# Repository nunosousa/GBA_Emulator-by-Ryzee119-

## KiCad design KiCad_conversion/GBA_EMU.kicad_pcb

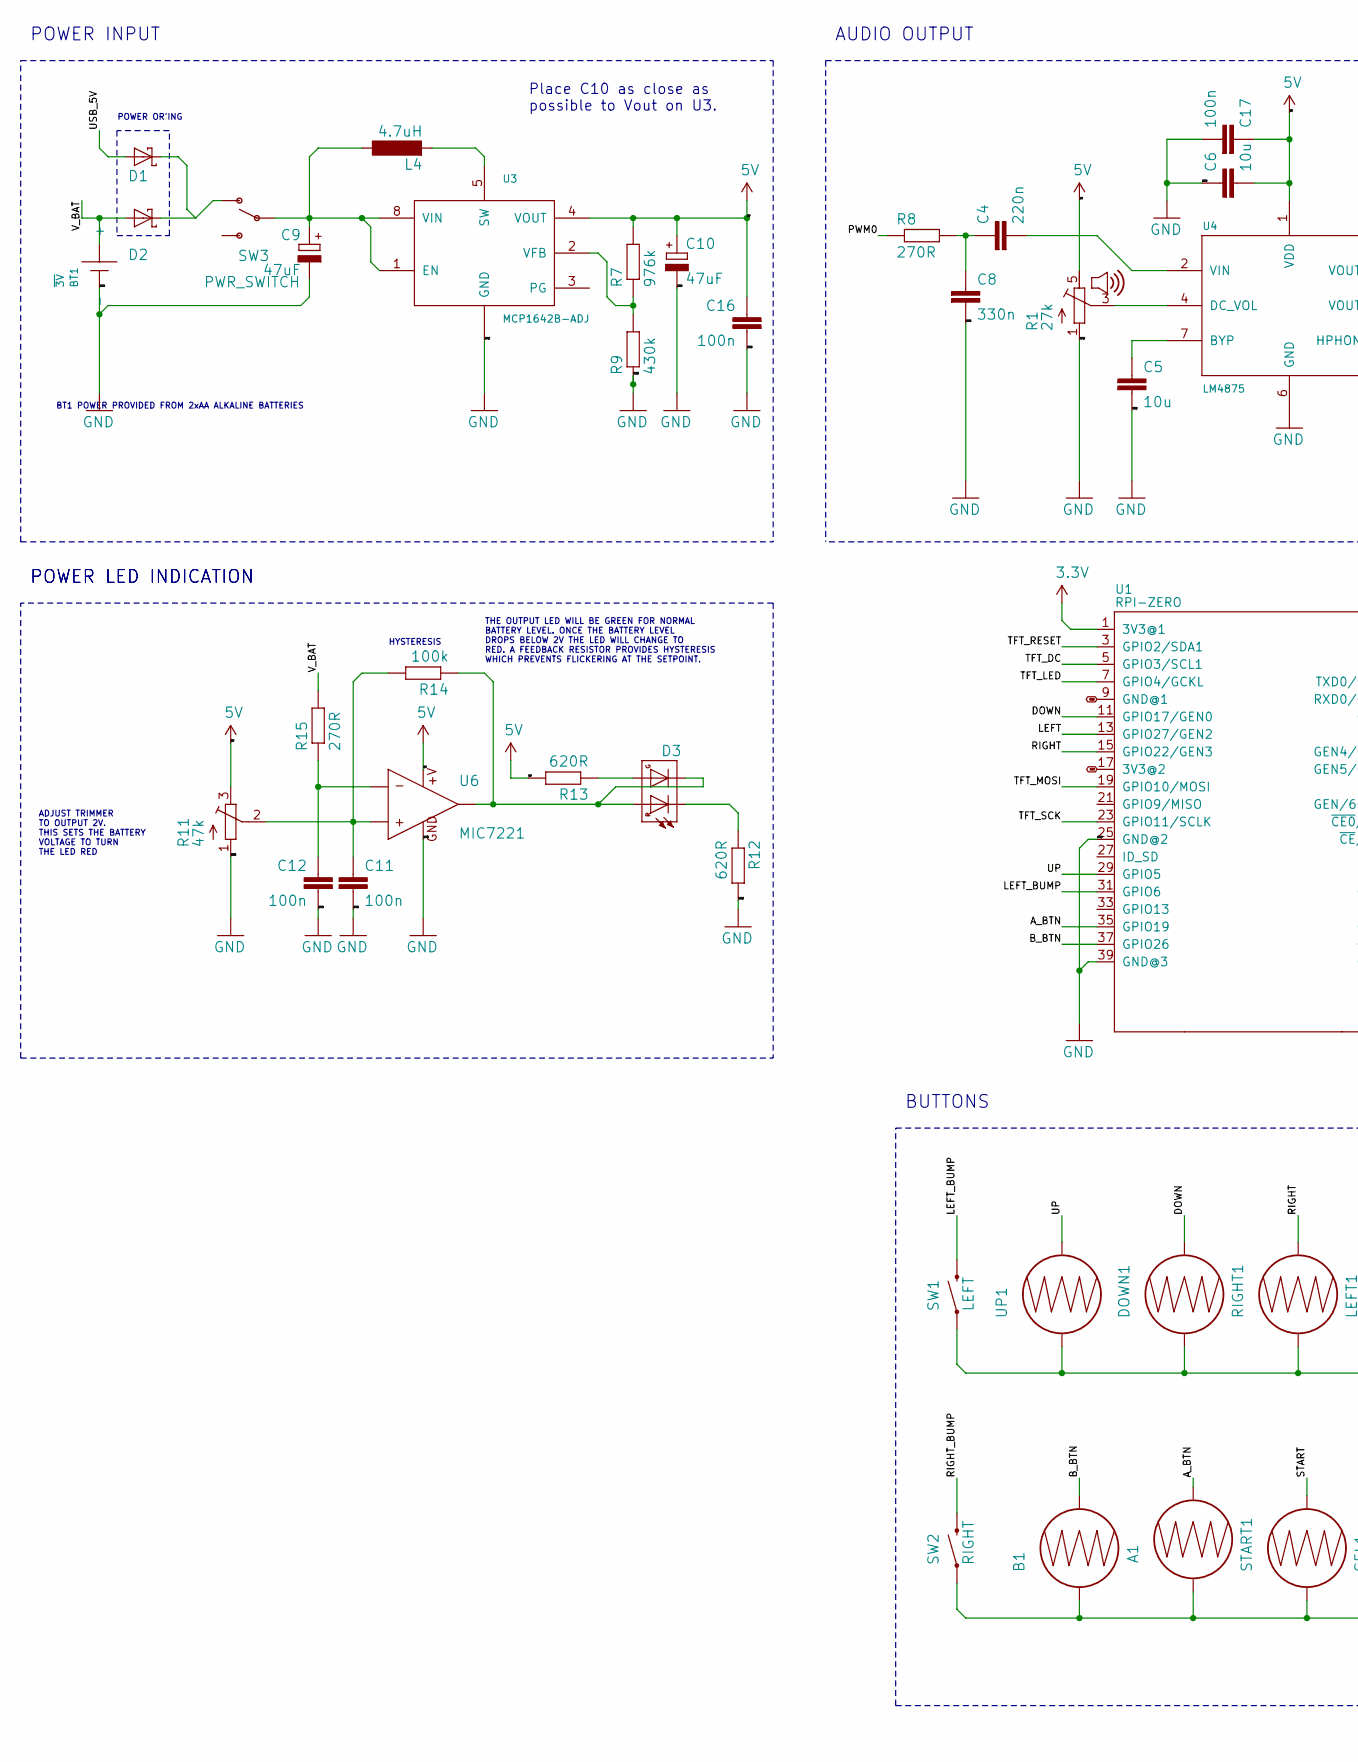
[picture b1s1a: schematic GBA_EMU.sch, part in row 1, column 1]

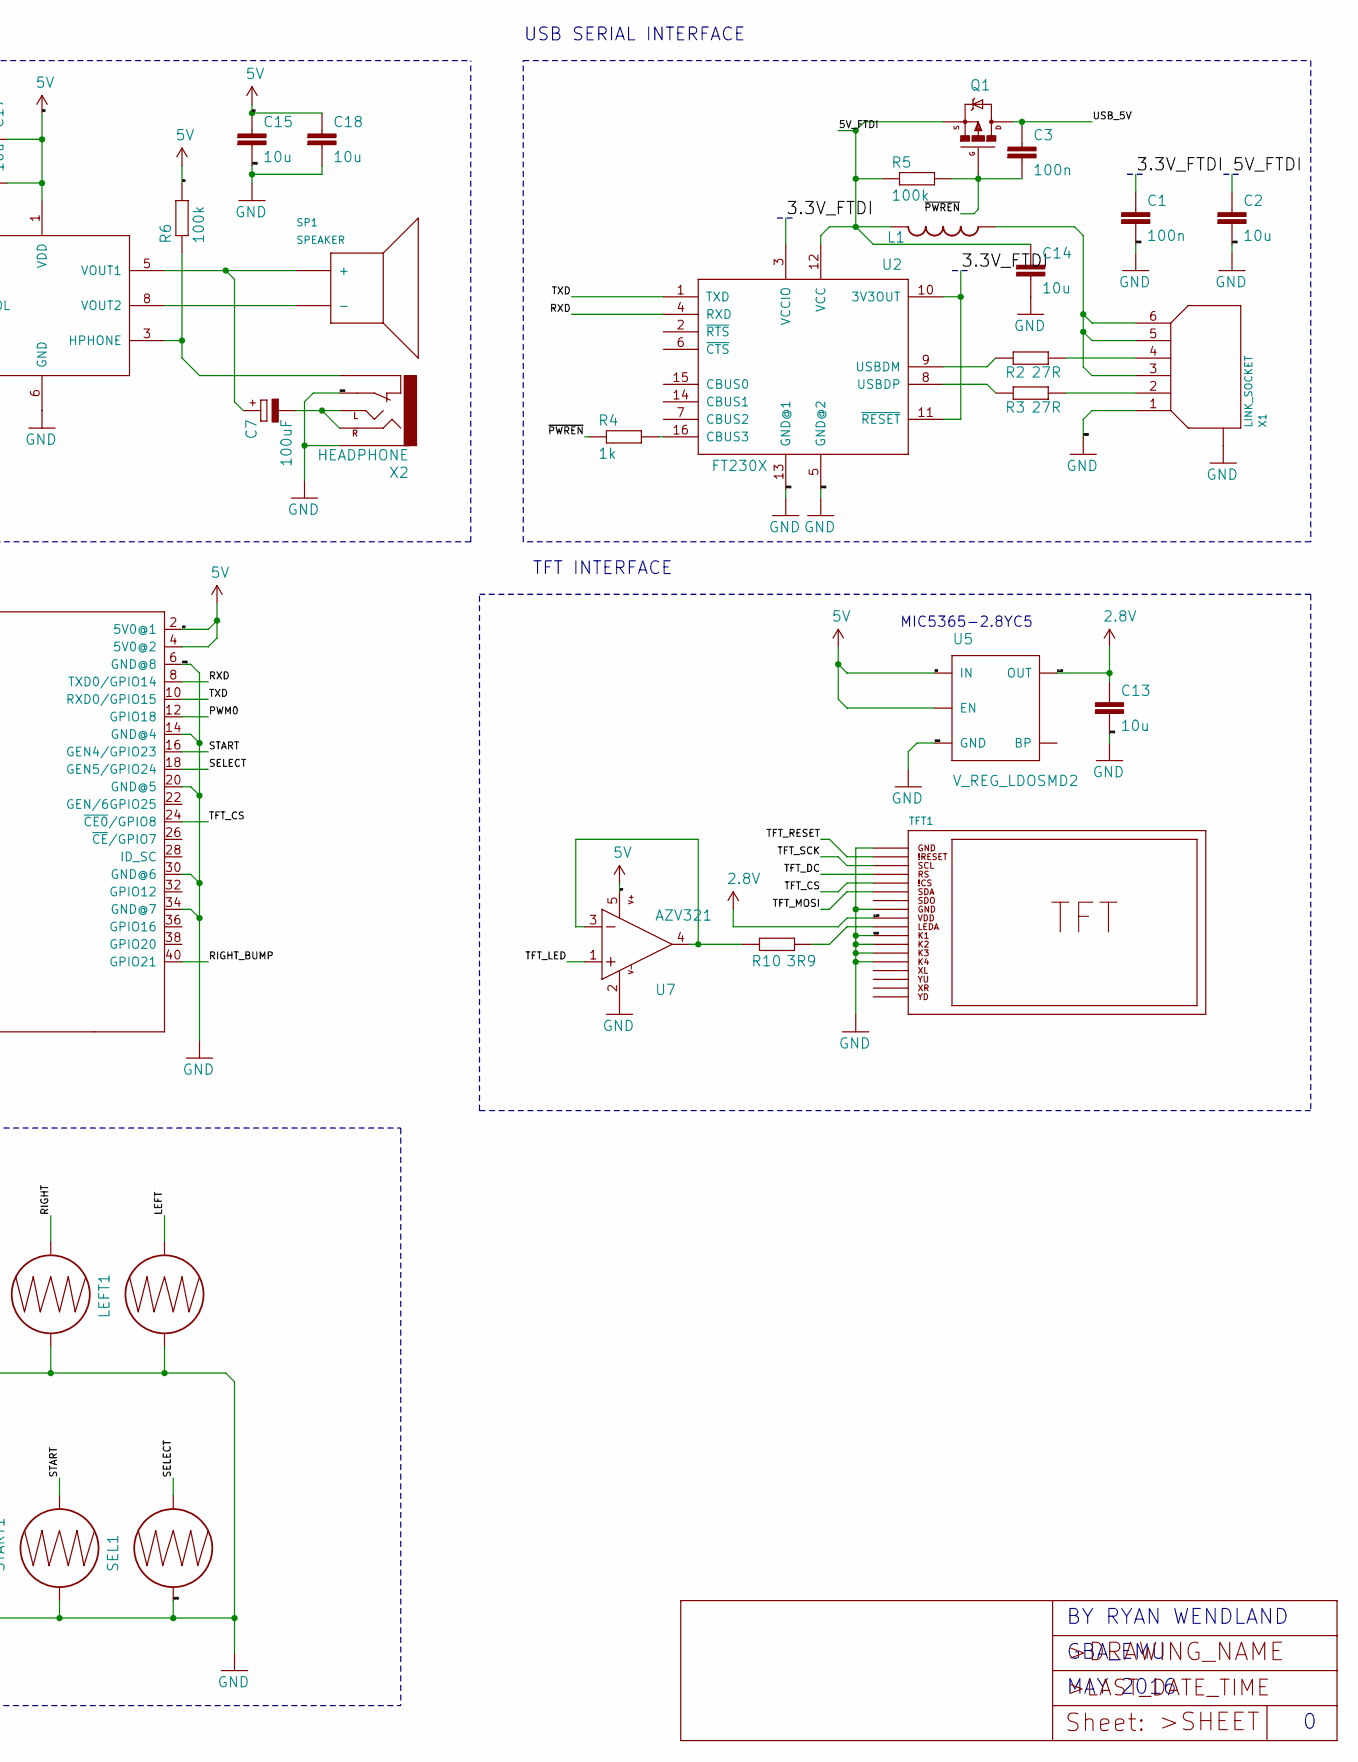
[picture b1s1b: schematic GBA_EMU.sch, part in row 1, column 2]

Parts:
A1: GBA_BTN_CONDUCTIVE; GBA_BUTTON_CONDUCTIVE
B1: GBA_BTN_CONDUCTIVE; GBA_BUTTON_CONDUCTIVE
BT1: ~3V; BATTERY
C1, C3, C11, C12, C16, C17: 100n; C0805
C2, C5, C6, C13, C14, C15, C18: 10u; C0805
C4: 220n; C0805
C7: 100uF; 153CLV-0405
C8: 330n; C0805
C9, C10: 47uF; 153CLV-0405
D1, D2: DFLS130L; POWERDI_123
D3: DUAL_LED
DOWN1: GBA_BTN_CONDUCTIVE; GBA_BUTTON_CONDUCTIVE
L1: 600; 0805
L4: 4.7uH; POWER-CHOKE_WE-TPC
LEFT1: GBA_BTN_CONDUCTIVE; GBA_BUTTON_CONDUCTIVE
Q1: MOSFET-PCHANNEL; SOT23-3
R1: 27k; VOLUME
R2, R3: 27R; R0805
R4: 1k; R0805
R5, R6, R14: 100k; R0805
R7: 976k; R0805
R8, R15: 270R; R0805
R9: 430k; R0805
R10: 3R9; R0805
R11: 47k; TC33X
R12, R13: 620R; R0805
RIGHT1: GBA_BTN_CONDUCTIVE; GBA_BUTTON_CONDUCTIVE
SEL1: BUTTON-CONDUCTIVESMD; BUTTON-CONDUCTIVE
SP1: SPEAKER
START1: BUTTON-CONDUCTIVESMD; BUTTON-CONDUCTIVE
SW1: LEFT; BUMPER
SW2: RIGHT; BUMPER
SW3: PWR_SWITCH
TFT1: GBA_TFT
U1: RPI-ZERO; RASPBERRYPI_BASTELSTUBE_V13_RASPI_BOARD_B+_FULL
U2: FT230X; SSOP16
U3: MCP1642B-ADJ; MSOP8
U4: LM4875; SOIC8
U5: V_REG_LDOSMD2; SC70
U6: MIC7221; SOT23-5
U7: AZV321; SOT23-5
UP1: GBA_BTN_CONDUCTIVE; GBA_BUTTON_CONDUCTIVE
X1: LINK_SOCKET
X2: HEADPHONE

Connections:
2.8V: C13.1, TFT1.9 (VDD), U5.5 (OUT)
3.3V: U1.1 (3V3@1)
3V3: U1.17 (3V3@2)
5V: C6.2, C10.+, C15.1, C16.1, C17.1, C18.1, R1.5 (E), R6.2, R7.2, R11.3 (E), R13.2, U1.2 (5V0@1), U1.4 (5V0@2), U3.4 (VOUT), U4.1 (VDD), U5.1 (IN), U5.3 (EN), U6.2 (+V), U7.5 (V+)
/3.3V_FTDI: C1.1, U2.3 (VCCIO), U2.10 (3V3OUT), U2.11 (~RESET)
/5V_FTDI: C2.1, C14.1, L1.1, Q1.2 (S), R5.1, U2.12 (VCC)
/A_BTN: A1.2, U1.35 (GPIO19)
/B_BTN: B1.2, U1.37 (GPIO26)
/DOWN: DOWN1.2, U1.11 (GPIO17/GEN0)
/LEFT: LEFT1.2, U1.13 (GPIO27/GEN2)
/LEFT_BUMP: SW1.2, U1.31 (GPIO6)
/PWM0: R8.1, U1.12 (GPIO18)
/RIGHT: RIGHT1.2, U1.15 (GPIO22/GEN3)
/RIGHT_BUMP: SW2.2, U1.40 (GPIO21)
/RXD: U1.8 (TXD0/GPIO14), U2.4 (RXD)
/SELECT: SEL1.2, U1.18 (GEN5/GPIO24)
/START: START1.2, U1.16 (GEN4/GPIO23)
/TFT_CS: TFT1.5 (~CS), U1.24 (~CE0~/GPIO8)
/TFT_DC: TFT1.4 (RS), U1.5 (GPIO3/SCL1)
/TFT_LED: U1.7 (GPIO4/GCKL), U7.1 (+IN)
/TFT_MOSI: TFT1.6 (SDA), U1.19 (GPIO10/MOSI)
/TFT_RESET: TFT1.2 (~RESET), U1.3 (GPIO2/SDA1)
/TFT_SCK: TFT1.3 (SCL), U1.23 (GPIO11/SCLK)
/TXD: U1.10 (RXD0/GPIO15), U2.1 (TXD)
/UP: U1.29 (GPIO5), UP1.2
/USB_5V: C3.1, D1.1 (A), Q1.3 (D)
/V_BAT: BT1.BT+1 (+), BT1.BT+2 (+), D2.1 (A), R15.2
/~PWREN: C3.2, Q1.1 (G), R4.1, R5.2
GND: A1.1, B1.1, BT1.BT-1 (-), BT1.BT-2 (-), C1.2, C2.2, C5.2, C6.1, C8.2, C9.-, C10.-, C11.2, C12.2, C13.2, C14.2, C15.2, C16.2, C17.2, C18.2, DOWN1.1, LEFT1.1, R1.1 (A), R9.1, R11.1 (A), R12.2, RIGHT1.1, SEL1.1, START1.1, SW1.1, SW2.1, TFT1.1 (GND@1), TFT1.8 (GND@2), TFT1.11 (K1), TFT1.12 (K2), TFT1.13 (K3), TFT1.14 (K4), U1.6 (GND@8), U1.9 (GND@1), U1.14 (GND@4), U1.20 (GND@5), U1.25 (GND@2), U1.30 (GND@6), U1.34 (GND@7), U1.39 (GND@3), U2.5 (GND@2), U2.13 (GND@1), U3.6 (GND), U3.7 (GND), U4.6 (GND), U5.2 (GND), U6.5 (GND), U7.2 (V-), UP1.1, X1.1, X1.GND@1 (GND), X1.GND@2 (GND), X2.1, X2.GND
unnamed: C4.1, C8.1, R8.2
unnamed: C4.2, U4.2 (VIN)
unnamed: C5.1, U4.7 (BYP)
unnamed: C7.+, SP1.1 (+), U4.5 (VOUT1)
unnamed: C7.-, X2.L (LEFT), X2.R (RIGHT)
unnamed: C9.+, L4.1, SW3.COM1, SW3.COM2, U3.1 (EN), U3.8 (VIN)
unnamed: C11.1, R11.2 (S), R14.2, U6.3 (+IN1)
unnamed: C12.1, R15.1, U6.4 (-IN1)
unnamed: D1.2 (C), D2.2 (C), SW3.1 (O)
unnamed: D3.1, D3.3, R14.1, U6.1 (OUT1)
unnamed: D3.2, R12.1
unnamed: D3.4, R13.1
unnamed: L1.2, X1.3, X1.5, X1.6
unnamed: L4.2, U3.5 (SW)
unnamed: R1.3 (S), U4.4 (DC_VOL)
unnamed: R2.1, U2.9 (USBDM)
unnamed: R2.2, X1.4
unnamed: R3.1, U2.8 (USBDP)
unnamed: R3.2, X1.2
unnamed: R4.2, U2.16 (CBUS3)
unnamed: R6.1, U4.3 (HPHONE), X2.2
unnamed: R7.1, R9.2, U3.2 (VFB)
unnamed: R10.1, U7.3 (-IN), U7.4 (OUT)
unnamed: R10.2, TFT1.10 (LEDA)
unnamed: SP1.2 (-), U4.8 (VOUT2)

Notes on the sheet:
USB SERIAL INTERFACE
AUDIO OUTPUT
POWER INPUT
POWER OR'ING
BT1 POWER PROVIDED FROM 2xAA ALKALINE BATTERIES
TFT INTERFACE
ADJUST TRIMMER TO OUTPUT 2V. THIS SETS THE BATTERY VOLTAGE TO TURN THE LED RED
HYSTERESIS
POWER LED INDICATION
THE OUTPUT LED WILL BE GREEN FOR NORMAL BATTERY LEVEL. ONCE THE BATTERY LEVEL DROPS BELOW 2V THE LED WILL CHANGE TO RED. A FEEDBACK RESISTOR PROVIDES HYSTERESIS WHICH PREVENTS FLICKERING AT THE SETPOINT.
GBA_EMU
MAY 2016
BY RYAN WENDLAND
BUTTONS
Place C10 as close as possible to Vout on U3.
MIC5365-2.8YC5

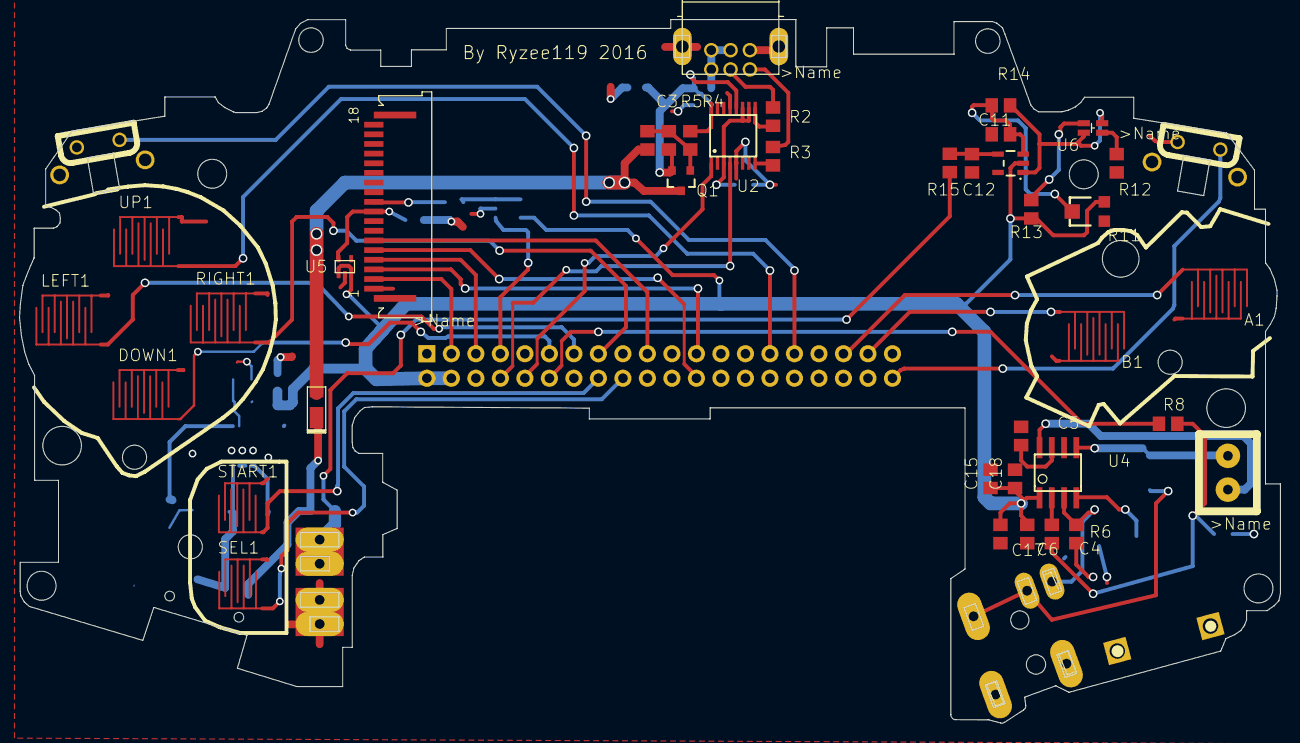
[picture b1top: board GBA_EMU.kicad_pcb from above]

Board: 2 copper layers, 130.7 x 72.9 mm, 74 parts (0 on the bottom side), 52 nets.

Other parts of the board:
@HOLE0, @HOLE1, @HOLE2, @HOLE3, @HOLE4, @HOLE5, @HOLE6, @HOLE7, @HOLE8, @HOLE9, @HOLE10, @HOLE11: (no value)

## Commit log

2020-08-30 Coverted existing Eagle project to KiCad.
